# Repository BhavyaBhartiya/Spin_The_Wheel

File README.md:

# Spin The Wheel

This project utilises a NE555 IC and a CD4017 IC to create an LED Wheel. When the user presses the start/stop button, the LEDs light up randomly. Pressing the start/stop button again reduces the speed at which the LEDs change, eventually leading to a stop.

## Schematic

## PCB

## BOM

| Designator | Value   |
| ---------- | ------- |
| BZ1        | Buzzer  |
| C1         | 10nf    |
| C2         | 100uf   |
| C3         | 100uf   |
| C6         | 470uf   |
| D1         | LED     |
| D2         | LED     |
| D3         | LED     |
| D4         | LED     |
| D5         | LED     |
| D6         | LED     |
| D7         | LED     |
| D8         | LED     |
| D9         | LED     |
| D10        | LED     |
| D11        | D       |
| J1         | USB_A   |
| Q1         | Q_PNP   |
| R1         | 9.5K    |
| R2         | 10K     |
| R3         | 1K      |
| R4         | 1K      |
| SW1        | Push    |
|            | Button  |
| U1         | NE555   |
| U2         | CD4017  |

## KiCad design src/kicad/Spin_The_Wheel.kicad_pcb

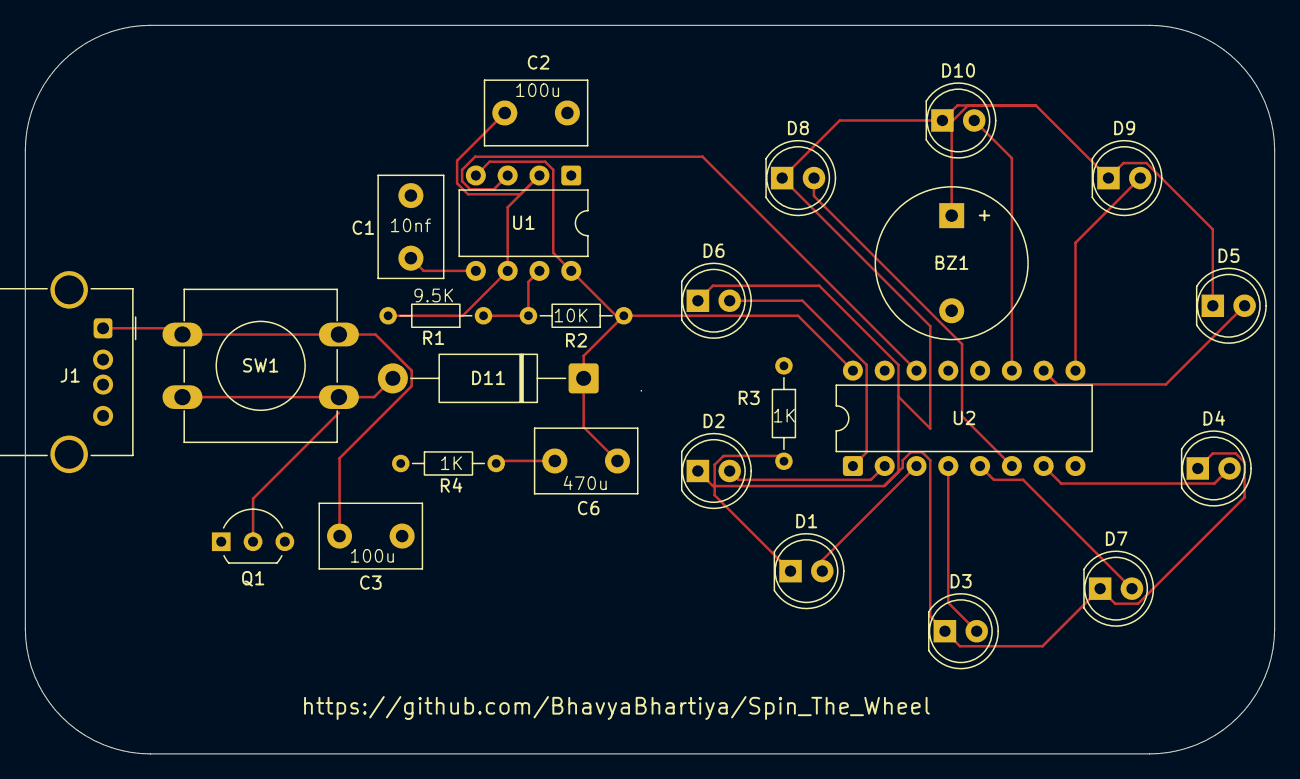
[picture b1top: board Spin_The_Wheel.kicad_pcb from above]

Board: 2 copper layers, 99.8 x 58.2 mm, 25 parts (0 on the bottom side), 20 nets.

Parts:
BZ1: Buzzer; Buzzer_12x9.5RM7.6
C1: 10nf; C_Disc_D8.0mm_W5.0mm_P5.00mm
C2, C3: 100uf; C_Disc_D8.0mm_W5.0mm_P5.00mm
C6: 470uf; C_Disc_D8.0mm_W5.0mm_P5.00mm
D1, D2, D3, D4, D5, D6, D7, D8, D9, D10: LED; LED_D5.0mm
D11: D; D_DO-15_P15.24mm_Horizontal
J1: USB_A; USB_A_Molex_67643_Horizontal
Q1: Q_PNP; TO-92L_Inline_Wide
R1: 9.5K; R_Axial_DIN0204_L3.6mm_D1.6mm_P7.62mm_Horizontal
R2: 10K; R_Axial_DIN0204_L3.6mm_D1.6mm_P7.62mm_Horizontal
R3, R4: 1K; R_Axial_DIN0204_L3.6mm_D1.6mm_P7.62mm_Horizontal
SW1: START/STOP; SW_PUSH-12mm
U1: ICM7555xB; DIP-8_W7.62mm
U2: 4017; DIP-16_W7.62mm

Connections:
GND: BZ1.2 (-), C1.2, C2.2, C3.1, J1.4 (GND), R3.1, R4.1, U1.1 (GND), U2.8 (VSS), U2.13 (CKEN), U2.15 (Reset)
unnamed: BZ1.1 (+), D1.1 (K), D2.1 (K), D3.1 (K), D4.1 (K), D5.1 (K), D6.1 (K), D7.1 (K), D8.1 (K), D9.1 (K), D10.1 (K), R3.2
unnamed: C6.2, R4.2
unnamed: D1.2 (A), U2.3 (Q0)
unnamed: D2.2 (A), U2.2 (Q1)
unnamed: D3.2 (A), U2.4 (Q2)
unnamed: D4.2 (A), U2.7 (Q3)
unnamed: D5.2 (A), U2.10 (Q4)
unnamed: D6.2 (A), U2.1 (Q5)
unnamed: D7.2 (A), U2.5 (Q6)
unnamed: D8.2 (A), U2.6 (Q7)
unnamed: D9.2 (A), U2.9 (Q8)
unnamed: D10.2 (A), U2.11 (Q9)
unnamed: D11.2 (A), SW1.2
unnamed: C3.2, J1.1 (VBUS), SW1.1
unnamed: C1.1, U1.5 (CONT)
unnamed: R1.1, R2.2, U1.7 (DISCH)
unnamed: U1.3 (OUT), U2.14 (CLK)
unnamed: C2.1, R1.2, U1.2 (TRIG), U1.6 (THRES)
VCC: C6.1, D11.1 (K), R2.1, U1.4 (~RST), U1.8 (VCC), U2.16 (VDD)

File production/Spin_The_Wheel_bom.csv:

Designator,Footprint,Quantity,Value,LCSC Part #
BZ1,Buzzer_12x9.5RM7.6,1,Buzzer,
C1,C_Disc_D8.0mm_W5.0mm_P5.00mm,1,10nf,
"C2, C3",C_Disc_D8.0mm_W5.0mm_P5.00mm,2,100uf,
C6,C_Disc_D8.0mm_W5.0mm_P5.00mm,1,470uf,
"D1, D10, D2, D3, D4, D5, D6, D7, D8, D9",LED_D5.0mm,10,LED,
D11,D_DO-15_P15.24mm_Horizontal,1,D,
J1,USB_A_Molex_67643_Horizontal,1,USB_A,
Q1,TO-92L_Inline_Wide,1,Q_PNP,
R1,R_Axial_DIN0204_L3.6mm_D1.6mm_P7.62mm_Horizontal,1,9.5K,
R2,R_Axial_DIN0204_L3.6mm_D1.6mm_P7.62mm_Horizontal,1,10K,
"R3, R4",R_Axial_DIN0204_L3.6mm_D1.6mm_P7.62mm_Horizontal,2,1K,
SW1,SW_PUSH-12mm,1,START/STOP,
U1,DIP-8_W7.62mm,1,ICM7555xB,
U2,DIP-16_W7.62mm,1,4017,

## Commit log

2026-04-11 Create a
2026-04-17 Reformat README.md for consistency
